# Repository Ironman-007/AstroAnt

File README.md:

# AstroAnt
Phase II of Rovables

The AstroAnt is the second generation of the Rovable project. The AstroAant also use magnetic wheels to attach to magnetic surface.

The AstroAnt is a modular design, and can carry different sensors to finish different kinds of diognostic missions, such as finding abnormal heating source, check CO2 leakage, detect metal flaw, and streaming video from remote.

Files descriptions:

- The 3D model of the robot is in the [Small_magnets_R821_with_gearbox](3dmodel/Small_magnets_R821_with_gearbox).

- The firmware of the robot is in [AstroAnt](Software/AstroAnt).

- The PC program (UI) is the [gui.py](Software/GUI_python/gui.py). Open with command line: ```python3 gui.py```

- The PCB design is in the [PCB](PCB). The [mainboard_v1](PCB/Mainboard/mainboard_v1/) is the design of the main control board, developed with KiCAD. The others are sensor modules design.

- The software of the central station for collecting data and distributing command is in [central_station](Software/Central_station/central_station/).

- The software of the central station for Camera in [cam_central](Software/Central_station/cam_central/).

- The Box design for the Zero-G flight test is in [Ant_Test_Box_DEC](3dmodel/Ant_Box_DEC/).

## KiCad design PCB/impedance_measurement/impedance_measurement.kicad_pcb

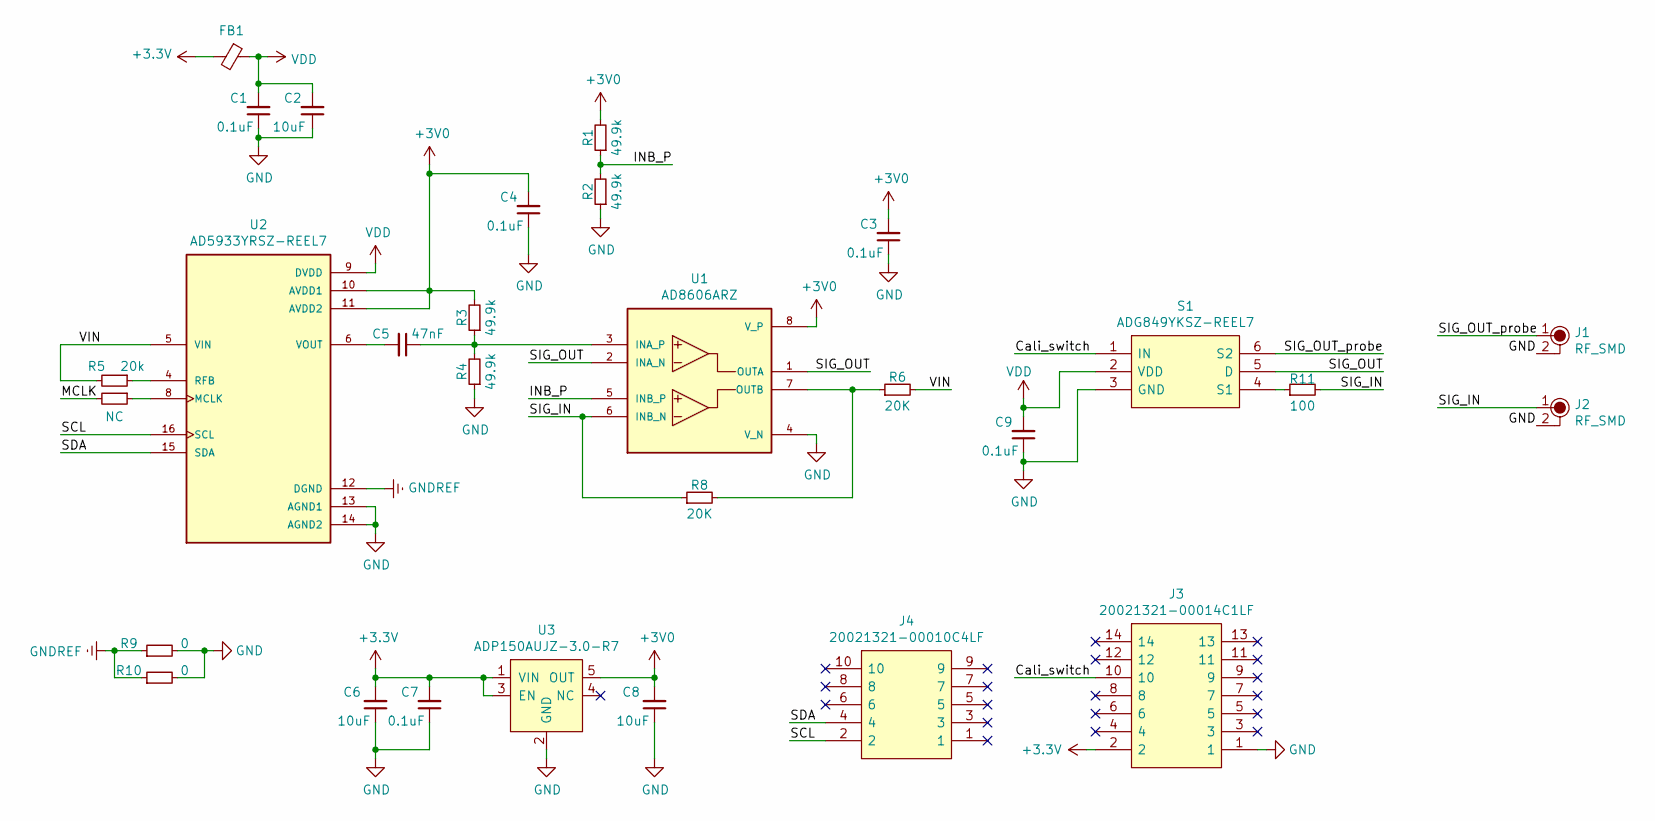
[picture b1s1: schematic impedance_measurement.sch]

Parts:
C1, C3, C4, C7, C9: 0.1uF; C_0603_1608Metric_Pad1.08x0.95mm_HandSolder
C2, C6, C8: 10uF; C_0603_1608Metric_Pad1.08x0.95mm_HandSolder
C5: 47nF; C_0402_1005Metric_Pad0.74x0.62mm_HandSolder
FB1: Ferrite_Bead_Small; C_0603_1608Metric_Pad1.08x0.95mm_HandSolder
J1, J2: RF_SMD
J3: 20021321-00014C1LF; PinHeader_2x07_P1.27mm_Vertical; Manufacturer_Part_Number 20021321-00014C1LF; Mouser Part Number 649-20213210014C1LF
J4: 20021321-00010C4LF; PinHeader_2x05_P1.27mm_Vertical; Manufacturer_Part_Number 20021321-00010C4LF; Mouser Part Number 649-202132100010C4LF
R1, R2, R3, R4: 49.9k; R_0402_1005Metric_Pad0.72x0.64mm_HandSolder
R5: 20k; R_0402_1005Metric_Pad0.72x0.64mm_HandSolder
R6: 20K; R_0402_1005Metric_Pad0.72x0.64mm_HandSolder
R7: NC; R_0402_1005Metric_Pad0.72x0.64mm_HandSolder
R8: 20K; R_0603_1608Metric_Pad0.98x0.95mm_HandSolder
R9, R10: 0; R_0402_1005Metric_Pad0.72x0.64mm_HandSolder
R11: 100; R_0805_2012Metric_Pad1.20x1.40mm_HandSolder
S1: ADG849YKSZ-REEL7; SOT65P210X110-6N; Manufacturer_Part_Number ADG849YKSZ-REEL7; Mouser Part Number 584-ADG849YKSZ-R7
U1: AD8606ARZ; SOIC127P600X175-8N; PARTREV Rev. O
U2: AD5933YRSZ-REEL7; SOP65P780X200-16N; PARTREV F
U3: ADP150AUJZ-3.0-R7; TSOT-23-5

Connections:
+3V0: C3.2, C4.2, C8.2, R1.2, R3.2, U1.8 (V_P), U2.10 (AVDD1), U2.11 (AVDD2), U3.5 (OUT)
+3V3: C6.2, C7.2, FB1.2, J3.2, U3.1 (VIN), U3.3 (EN)
/Cali_switch: J3.10, S1.1 (IN)
/INB_P: R1.1, R2.2, U1.5 (INB_P)
/SCL: J4.2, U2.16 (SCL)
/SDA: J4.4, U2.15 (SDA)
/SIG_IN: J2.1, R8.1, R11.2, U1.6 (INB_N)
/SIG_OUT: S1.5 (D), U1.1 (OUTA), U1.2 (INA_N)
/SIG_OUT_probe: J1.1, S1.6 (S2)
/VIN: R5.2, R6.2, U2.5 (VIN)
GND: C1.1, C2.1, C3.1, C4.1, C6.1, C7.1, C8.1, C9.1, J1.2, J2.2, J3.1, R2.1, R4.1, R9.2, R10.2, S1.3 (GND), U1.4 (V_N), U2.13 (AGND1), U2.14 (AGND2), U3.2 (GND)
GNDREF: R9.1, R10.1, U2.12 (DGND)
unnamed: C5.1, R3.1, R4.2, U1.3 (INA_P)
unnamed: C5.2, U2.6 (VOUT)
unnamed: R5.1, U2.4 (RFB)
unnamed: R6.1, R8.2, U1.7 (OUTB)
unnamed: R7.1, U2.8 (MCLK)
unnamed: R11.1, S1.4 (S1)
VDD: C1.2, C2.2, C9.2, FB1.1, S1.2 (VDD), U2.9 (DVDD)

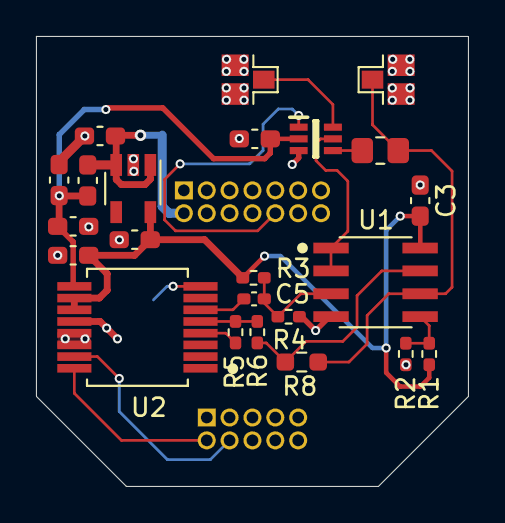
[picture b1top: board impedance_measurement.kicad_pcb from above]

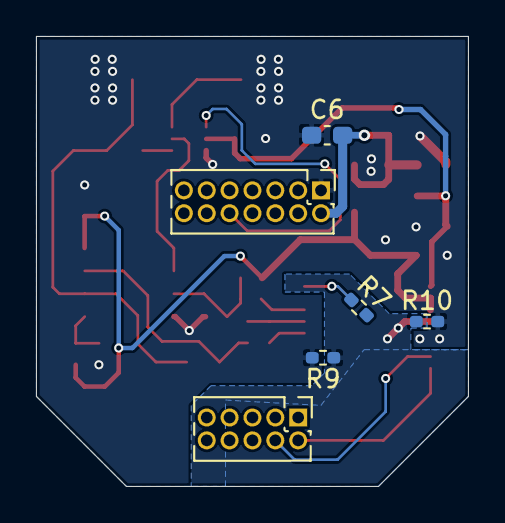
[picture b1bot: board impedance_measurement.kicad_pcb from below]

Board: 2 copper layers, 24.0 x 25.0 mm, 29 parts (6 on the bottom side), 19 nets.

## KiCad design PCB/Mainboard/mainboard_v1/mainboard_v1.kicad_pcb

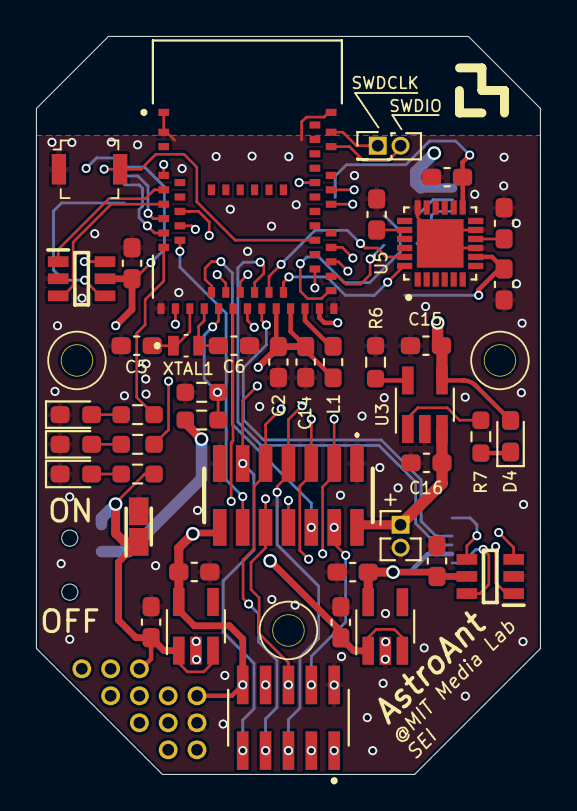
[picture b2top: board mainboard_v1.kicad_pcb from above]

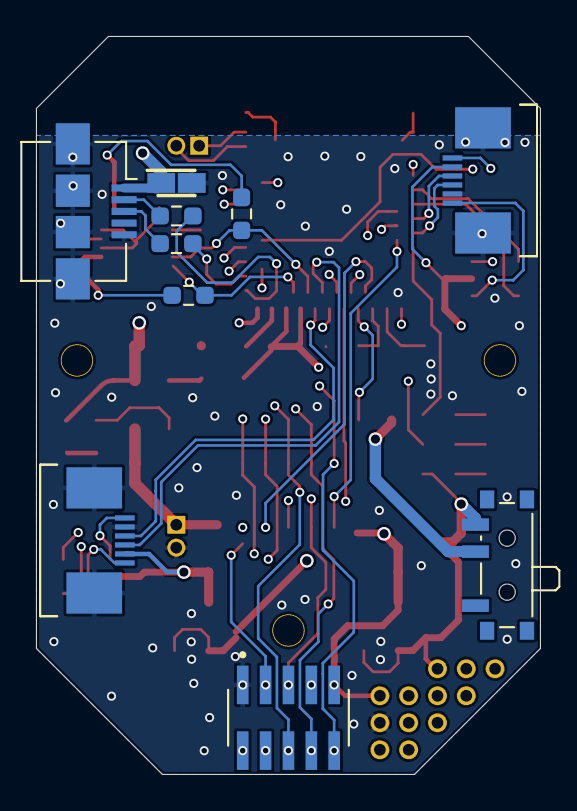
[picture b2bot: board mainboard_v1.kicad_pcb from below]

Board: 4 copper layers, 28.0 x 41.0 mm, 67 parts (10 on the bottom side), 54 nets.

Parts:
C1, C4, C8, C11, C12, C18: 0.1uF; C_0603_1608Metric_Pad1.08x0.95mm_HandSolder
C2, C10, C14, C15, C16, C17: 10uF; C_0603_1608Metric_Pad1.08x0.95mm_HandSolder
C3: 10000pF; C_0603_1608Metric_Pad1.08x0.95mm_HandSolder
C5, C6: 22PF; C_0603_1608Metric_Pad1.08x0.95mm_HandSolder
C7: 2200pF; C_0603_1608Metric_Pad1.08x0.95mm_HandSolder
C9, C13: TAJP106K010RNJ; CAPPM2014X170N
D1: LED_white; LED_0603_1608Metric_Pad1.05x0.95mm_HandSolder
D2: LED_red; LED_0603_1608Metric_Pad1.05x0.95mm_HandSolder
D3, D4: LED; LED_0603_1608Metric_Pad1.05x0.95mm_HandSolder
H1, H2, H3: M2; mounthole_1.8mm
IC1, IC2: MP6513GJ-Z; SOT95P280X100-6N
J1: 22-23-2021; PinHeader_1x02_P1.27mm_Vertical
J2: USB_B_Micro; USB_Micro-B_Amphenol_10104110_Horizontal
J3, J8: 1734592-6; 17345926
J4: 22-23-2021; PinHeader_2x01_P1.27mm_Vertical
J5, J7: 20021321-00010C4LF; HARWIN_M50-3100545
J6: 20021321-00014C1LF; 2002132100014C1LF
J9, J10, J11, J12, J13, J14, J15, J16, J17, J18, J19, J20: 1_pin_sig; 1.27mm_pin_hole
L1: 10uH; L_0603_1608Metric_Pad1.05x0.95mm_HandSolder
R1, R2: 49.9k; R_0603_1608Metric_Pad0.98x0.95mm_HandSolder
R3, R4, R5, R6: 4.99k; R_0603_1608Metric_Pad0.98x0.95mm_HandSolder
R7: 1k; R_0603_1608Metric_Pad0.98x0.95mm_HandSolder
R8, R9: 27; R_0603_1608Metric_Pad0.98x0.95mm_HandSolder
R10, R11: 10k; R_0603_1608Metric_Pad0.98x0.95mm_HandSolder
S1: B3U-1000P; Switch_Tactile_SMD_B3U-1000P
SW1: SW_SPDT; SW_SPDT_PCM12
U1: MDBT50Q-1MV2; XCVR_MDBT50Q-1MV2
U3: MCP73831T-2ACI_OT; SOT-23-5_HandSoldering
U4, U7: AP2112K-3.3; SOT-23-5_HandSoldering
U5: MPU6050; IC_MPU6050
XTAL1: 32.768KHz; ECS32712512TR

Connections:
+3V3: C1.2, C2.2, C3.2, C10.2, C14.2, J5.10, J6.14, J7.9, J11.1, L1.1, R10.2, R11.2, U1.28, U1.30, U4.5, U5.8, U5.13
/A0: R1.1, R2.2, U1.20
/A1: J5.8, J7.7, U1.21
/A3: J6.12, U1.13
/A5: J9.1, U1.9
/D5: J8.4, U1.25
/D6: J5.6, J6.10, J7.5, U1.23
/D9: J6.6, U1.19
/D11: J5.4, J6.4, J7.3, U1.22
/D12: J6.8, U1.24
/D13: J8.3, U1.26
/GP0: J18.1, U1.4
/GP2: J19.1, U1.11
/LED1: R3.2, U1.14
/LED2: R4.2, U1.16
/M1_IN1: IC1.1, U1.6
/M1_IN2: IC1.3, U1.8
/M1_O1: IC1.6, J3.6
/M1_O2: IC1.4, J3.1
/M2_IN1: IC2.1, U1.44
/M2_IN2: IC2.3, U1.46
/M2_O1: IC2.6, J8.6
/M2_O2: IC2.4, J8.1
/MISO: J5.1, J6.3, J7.2, U1.39
/MOSI: J5.3, J6.5, J7.4, U1.37
/MOTOR1_A: J3.4, U1.10
/MOTOR1_B: J3.3, U1.12
/SCK: J5.5, J6.7, J7.6, U1.36
/SCL: J5.9, J6.11, J7.10, R10.1, U1.27, U5.23
/SDA: J5.7, J6.9, J7.8, R11.1, U1.29, U5.24
/SWDCLK: J4.1, U1.53
/SWDIO: J4.2, U1.51
/SWO: J15.1, U1.47
/USB+: J2.3, R8.1
/USB-: J2.2, R9.1
/~RESET: J17.1, S1.2, U1.40
GND: C1.1, C2.1, C3.1, C4.1, C5.2, C6.2, C7.1, C8.1, C9.2, C10.1, C11.1, C12.1, C13.2, C14.1, C15.1, C16.1, C17.1, C18.1, D1.1, D2.1, D3.1, IC1.2, IC2.2, J1.2, J2.5, J2.6, J3.2, J3.MP1, J3.MP2, J5.2, J6.1, J6.13, J7.1, J8.2, J8.MP1, J8.MP2, J14.1, R2.1, R6.2, S1.1, U1.1, U1.2, U1.15, U1.33, U1.55, U3.2, U4.2, U5.9, U5.11, U5.18, U5.25, U7.2
unnamed: C4.2, U5.10
unnamed: C5.1, U1.17, XTAL1.1
unnamed: C6.1, U1.18, XTAL1.2
unnamed: C7.2, U5.20
unnamed: C9.1, C11.2, C18.2, J20.1, R5.1, SW1.3, U4.1, U4.3, U7.1, U7.3
unnamed: D1.2, R3.1
unnamed: D2.2, R4.1
unnamed: D3.2, R5.2
unnamed: D4.1, R7.1
unnamed: L1.2, U1.31
unnamed: R6.1, U3.5
unnamed: R7.2, U3.1
unnamed: R8.2, U1.35
unnamed: R9.2, U1.34
VBUS: C13.1, C15.2, D4.2, J2.1, U1.32, U3.4
VCC: C8.2, C12.2, C17.2, IC1.5, IC2.5, J3.5, J8.5, U7.5
VPP: C16.2, J1.1, J6.2, R1.2, SW1.2, U3.3

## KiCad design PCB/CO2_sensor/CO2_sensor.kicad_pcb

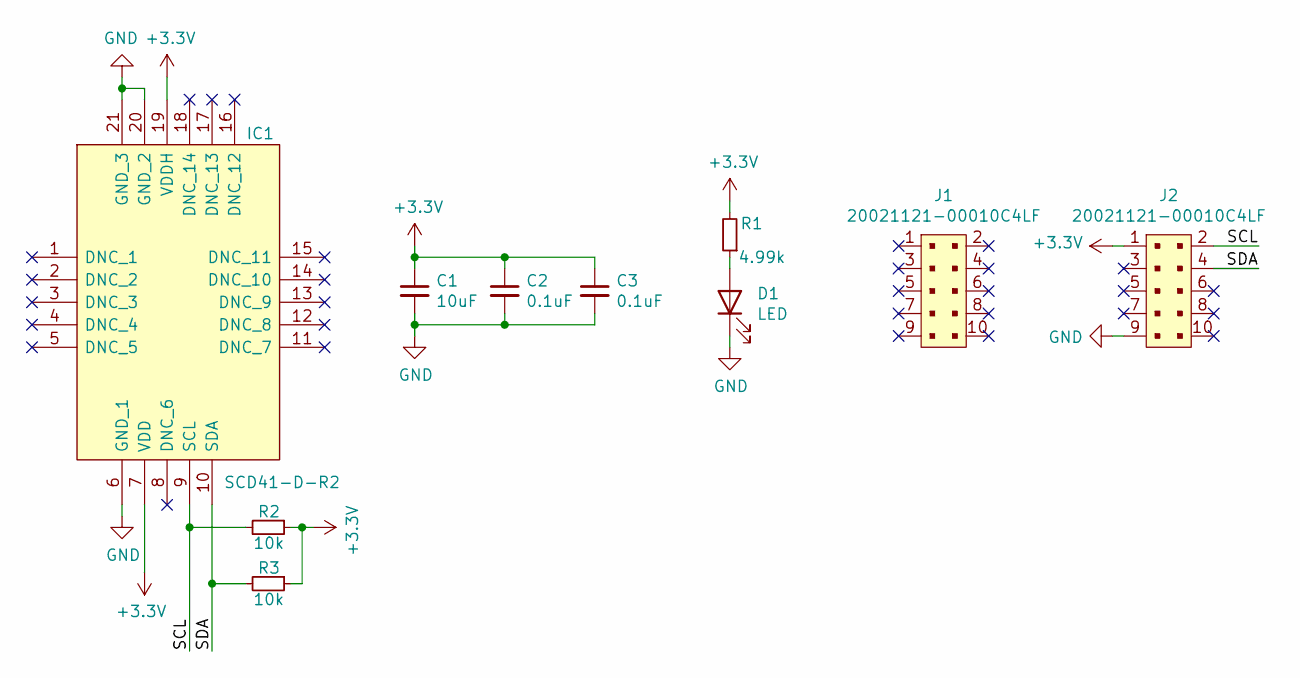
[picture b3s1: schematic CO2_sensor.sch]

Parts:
C1: 10uF; C_0603_1608Metric_Pad1.08x0.95mm_HandSolder
C2, C3: 0.1uF; C_0603_1608Metric_Pad1.08x0.95mm_HandSolder
D1: LED; LED_0603_1608Metric_Pad1.05x0.95mm_HandSolder
IC1: SCD41-D-R2; SCD41DR2; Manufacturer_Part_Number SCD41-D-R2; Mouser Part Number 403-SCD41-D-R2
J1, J2: 20021121-00010C4LF; PinHeader_2x5_P1.27mm; MPN 20021121-00010C4LF; Digi-Key_PN 609-3695-1-ND
R1: 4.99k; R_0603_1608Metric_Pad0.98x0.95mm_HandSolder
R2, R3: 10k; R_0603_1608Metric_Pad0.98x0.95mm_HandSolder

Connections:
+3V3: C1.1, C2.1, C3.1, IC1.7 (VDD), IC1.19 (VDDH), J2.1, R1.2, R2.1, R3.1
/SCL: IC1.9 (SCL), J2.2, R2.2
/SDA: IC1.10 (SDA), J2.4, R3.2
GND: C1.2, C2.2, C3.2, D1.1 (K), IC1.6 (GND_1), IC1.20 (GND_2), IC1.21 (GND_3), J2.9
unnamed: D1.2 (A), R1.1

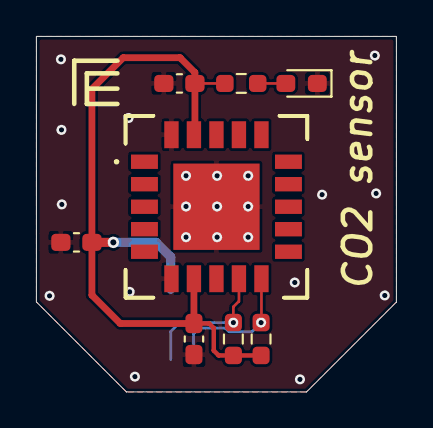
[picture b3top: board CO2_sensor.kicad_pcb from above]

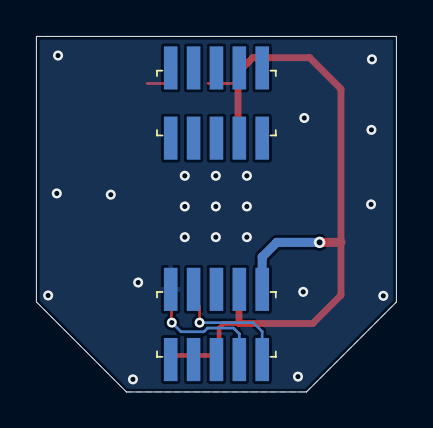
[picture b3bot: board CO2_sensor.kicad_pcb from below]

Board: 2 copper layers, 20.0 x 19.8 mm, 10 parts (2 on the bottom side), 5 nets.

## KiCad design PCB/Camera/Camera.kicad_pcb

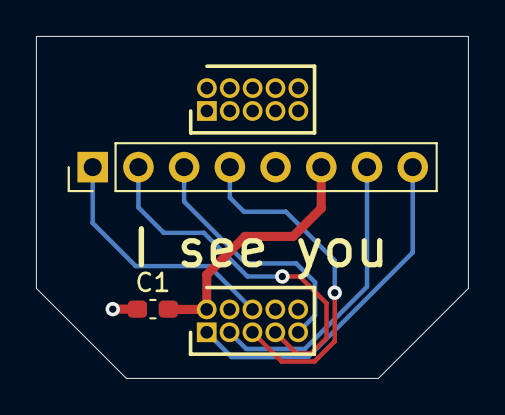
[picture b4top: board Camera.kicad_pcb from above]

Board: 2 copper layers, 24.0 x 19.0 mm, 4 parts (0 on the bottom side), 8 nets.

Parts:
C1: 0.1uF; C_0603_1608Metric_Pad1.08x0.95mm_HandSolder
J1, J2: GRPB052VWVN-RC; HDRV10W50P127_2X5_635X340X430P
U1: Arducam_OV2640_module; PinHeader_1x08_P2.54mm_Vertical

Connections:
+3V3: C1.1, J1.2, U1.6
/CS: J1.6, U1.1
/MISO: J1.9, U1.3
/MOSI: J1.7, U1.2
/SCK: J1.5, U1.4
/SCL: J1.1, U1.8
/SDA: J1.3, U1.7
GND: C1.2, J1.10, U1.5

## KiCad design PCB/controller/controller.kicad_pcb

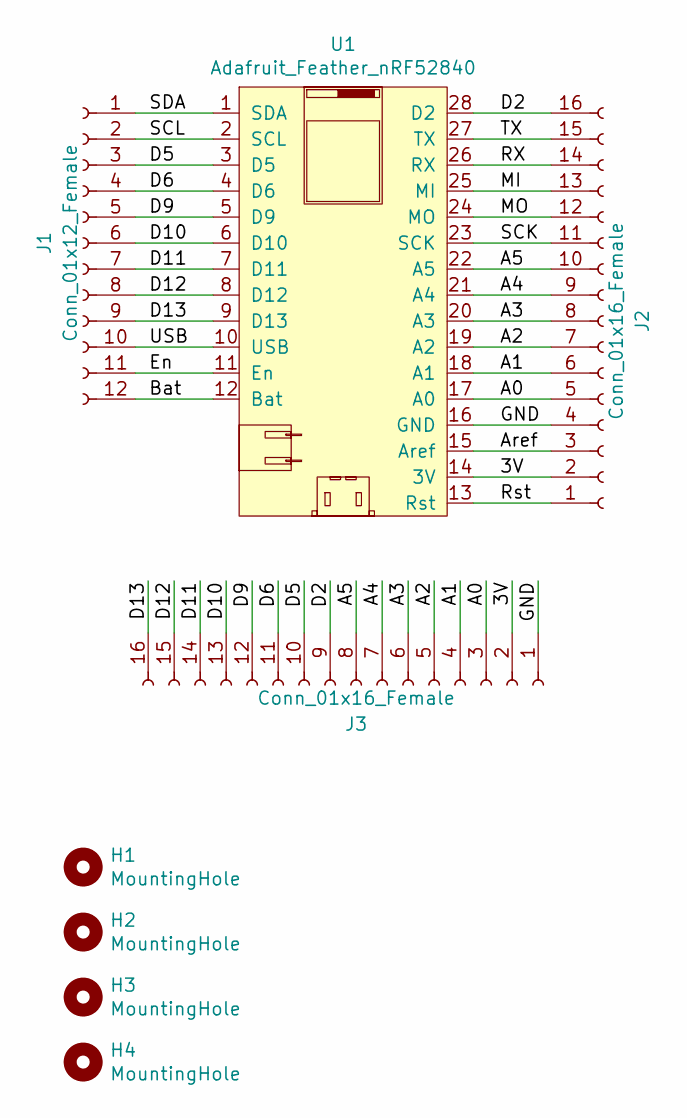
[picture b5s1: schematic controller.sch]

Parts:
H1, H2, H3, H4: MountingHole; MountingHole_2.2mm_M2
J1: Conn_01x12_Female; PinHeader_1x12_P2.54mm_Vertical
J2: Conn_01x16_Female; PinHeader_1x16_P2.54mm_Vertical
J3: Conn_01x16_Female; PinHeader_1x16_P2.54mm_Horizontal
U1: Adafruit_Feather_nRF52840; Adafruit_feather_nRF52840

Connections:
/3V: J2.2, J3.2, U1.14 (3V)
/A0: J2.5, J3.3, U1.17 (A0)
/A1: J2.6, J3.4, U1.18 (A1)
/A2: J2.7, J3.5, U1.19 (A2)
/A3: J2.8, J3.6, U1.20 (A3)
/A4: J2.9, J3.7, U1.21 (A4)
/A5: J2.10, J3.8, U1.22 (A5)
/Aref: J2.3, U1.15 (Aref)
/Bat: J1.12, U1.12 (Bat)
/D2: J2.16, J3.9, U1.28 (D2)
/D5: J1.3, J3.10, U1.3 (D5)
/D6: J1.4, J3.11, U1.4 (D6)
/D9: J1.5, J3.12, U1.5 (D9)
/D10: J1.6, J3.13, U1.6 (D10)
/D11: J1.7, J3.14, U1.7 (D11)
/D12: J1.8, J3.15, U1.8 (D12)
/D13: J1.9, J3.16, U1.9 (D13)
/En: J1.11, U1.11 (En)
/GND: J2.4, J3.1, U1.16 (GND)
/MI: J2.13, U1.25 (MI)
/MO: J2.12, U1.24 (MO)
/RX: J2.14, U1.26 (RX)
/Rst: J2.1, U1.13 (Rst)
/SCK: J2.11, U1.23 (SCK)
/SCL: J1.2, U1.2 (SCL)
/SDA: J1.1, U1.1 (SDA)
/TX: J2.15, U1.27 (TX)
/USB: J1.10, U1.10 (USB)

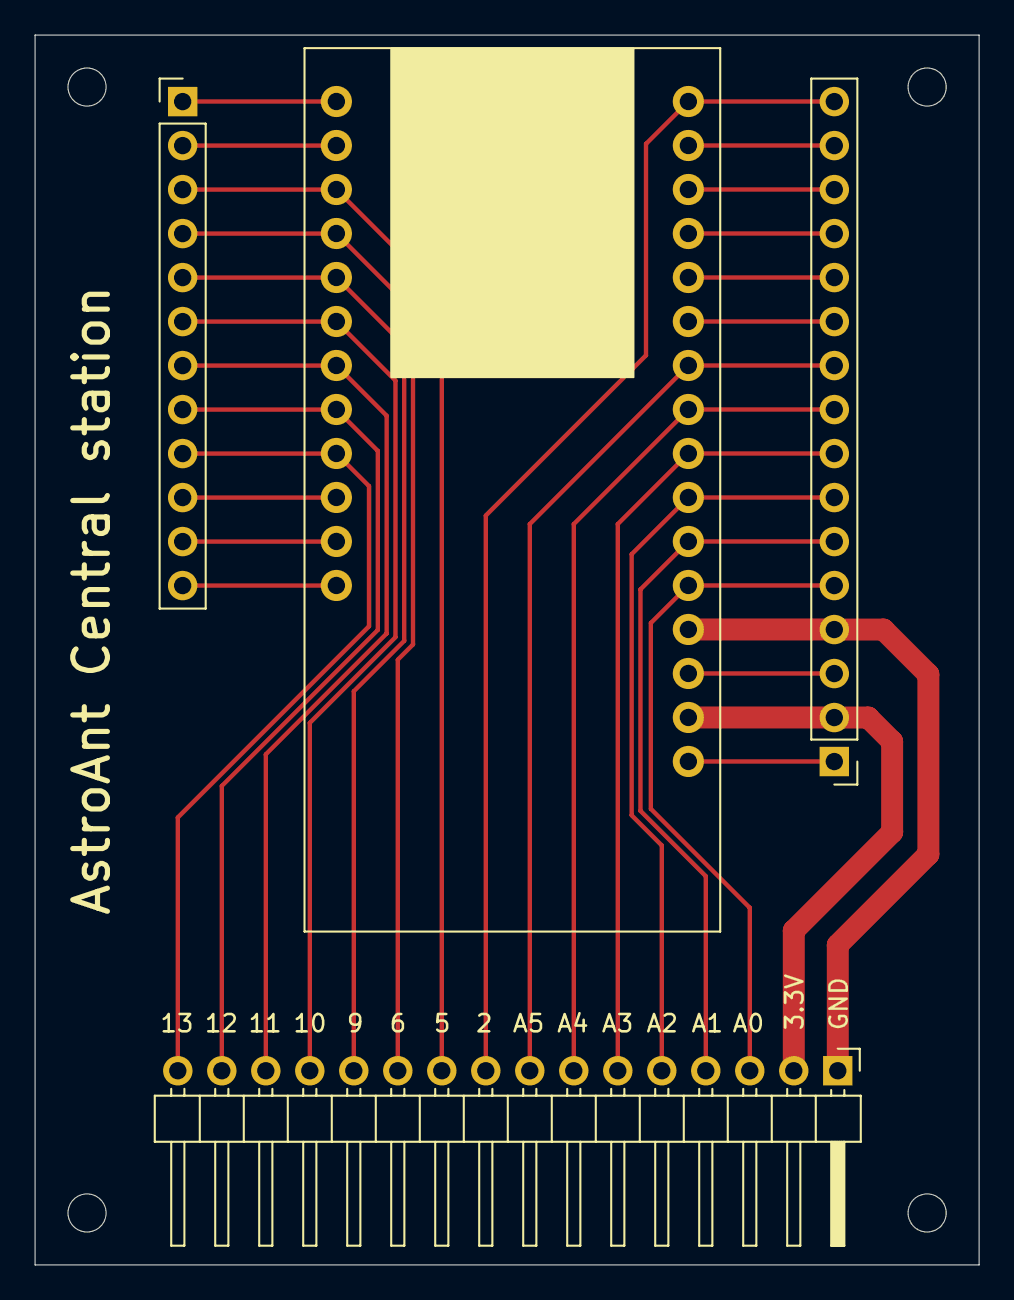
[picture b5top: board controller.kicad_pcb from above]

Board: 2 copper layers, 54.5 x 71.0 mm, 8 parts (0 on the bottom side), 28 nets.

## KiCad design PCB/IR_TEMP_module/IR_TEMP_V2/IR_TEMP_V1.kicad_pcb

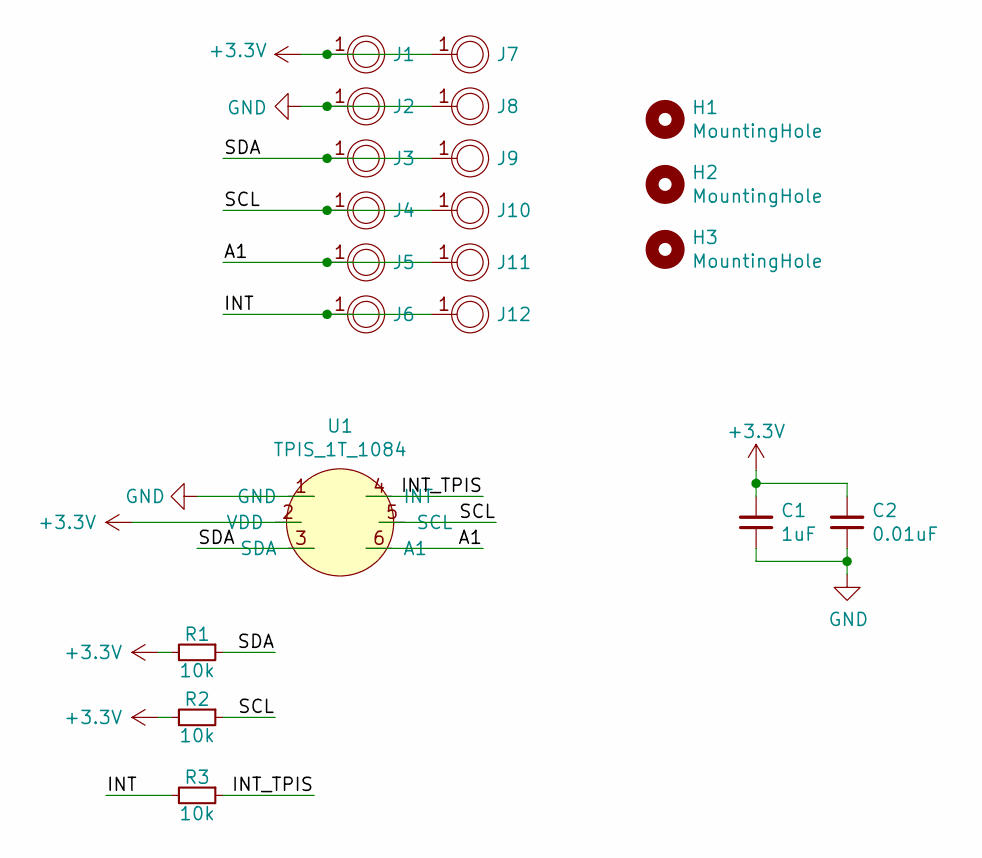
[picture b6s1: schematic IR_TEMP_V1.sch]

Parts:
C1: 1uF; C_0402_1005Metric_Pad0.74x0.62mm_HandSolder
C2: 0.01uF; C_0402_1005Metric_Pad0.74x0.62mm_HandSolder
H1, H2, H3: MountingHole; M1.6_mounthole
J1, J2, J3, J4, J5, J6, J7, J8, J9, J10, J11, J12: 1_PIN; 1_pin_SMD_1.5mmx1.0mm
R1, R2, R3: 10k; R_0402_1005Metric_Pad0.72x0.64mm_HandSolder
U1: TPIS_1T_1084

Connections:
+3V3: C1.2, C2.2, J1.1, J7.1, R1.2, R2.2, U1.2 (VDD)
/A1: J5.1, J11.1, U1.6 (A1)
/INT: J6.1, J12.1, R3.2
/INT_TPIS: R3.1, U1.4 (INT)
/SCL: J4.1, J10.1, R2.1, U1.5 (SCL)
/SDA: J3.1, J9.1, R1.1, U1.3 (SDA)
GND: C1.1, C2.1, J2.1, J8.1, U1.1 (GND)

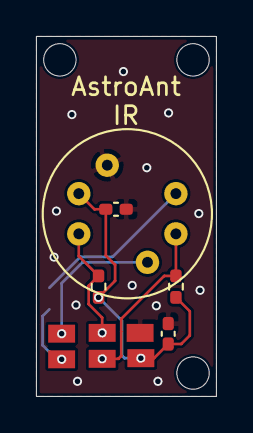
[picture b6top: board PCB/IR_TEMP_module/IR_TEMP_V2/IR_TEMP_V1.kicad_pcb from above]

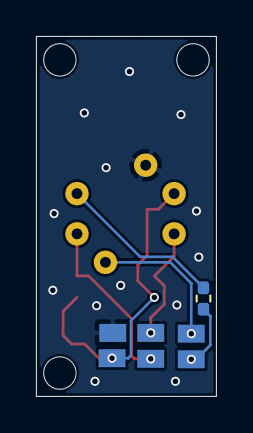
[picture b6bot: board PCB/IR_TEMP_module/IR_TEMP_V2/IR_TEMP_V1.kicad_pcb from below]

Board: 2 copper layers, 10.0 x 20.0 mm, 21 parts (7 on the bottom side), 7 nets.

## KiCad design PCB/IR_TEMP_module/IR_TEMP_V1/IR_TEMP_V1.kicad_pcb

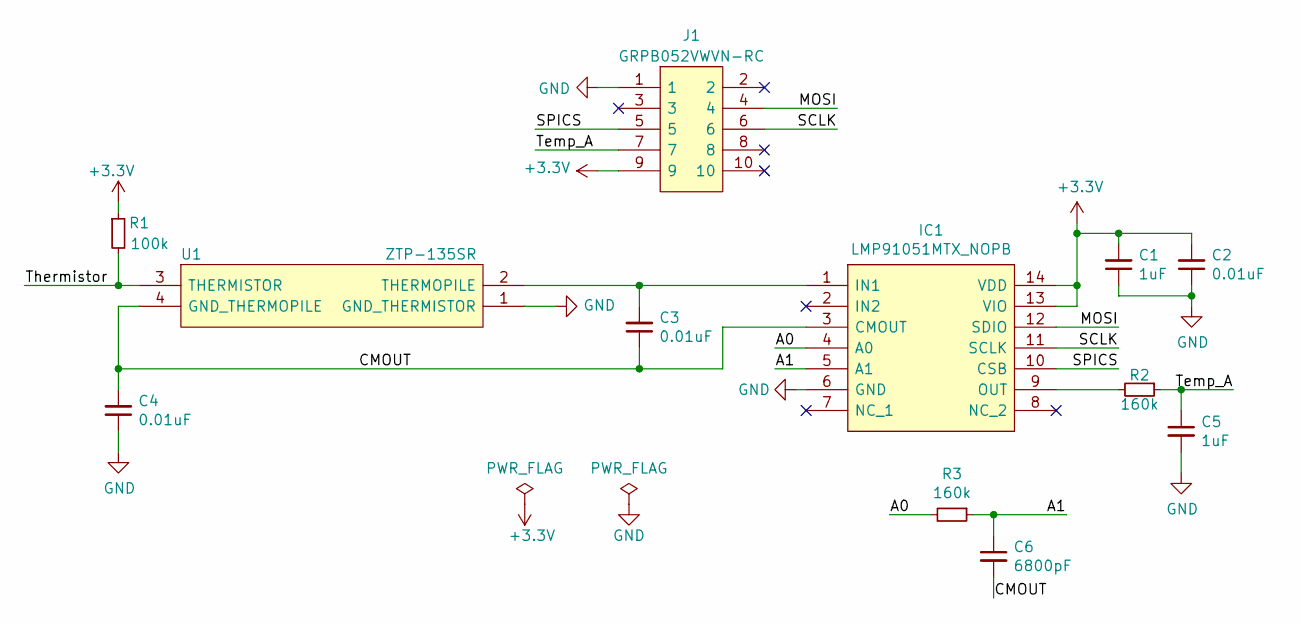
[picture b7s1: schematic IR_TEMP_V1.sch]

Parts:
C1, C5: 1uF; C_0402_1005Metric_Pad0.74x0.62mm_HandSolder
C2, C3, C4: 0.01uF; C_0402_1005Metric_Pad0.74x0.62mm_HandSolder
C6: 6800pF; C_0603_1608Metric_Pad1.08x0.95mm_HandSolder
IC1: LMP91051MTX_NOPB; SOP65P640X120-14N; Manufacturer_Part_Number LMP91051MTX/NOPB; Mouser Part Number 595-LMP91051MTX/NOPB
J1: GRPB052VWVN-RC; HDRV10W50P127_2X5_635X340X430P; Manufacturer_Part_Number GRPB052VWVN-RC
R1: 100k; R_0402_1005Metric_Pad0.72x0.64mm_HandSolder
R2: 160k; R_0402_1005Metric_Pad0.72x0.64mm_HandSolder
R3: 160k; R_0603_1608Metric_Pad0.98x0.95mm_HandSolder
U1: ZTP-135SR; TO-46-4; Manufacturer_Part_Number ZTP-135SR; Mouser Part Number 527-ZTP-135SR

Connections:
+3V3: C1.2, C2.2, IC1.13 (VIO), IC1.14 (VDD), J1.9, R1.1
/A0: IC1.4 (A0), R3.2
/A1: C6.1, IC1.5 (A1), R3.1
/CMOUT: C3.1, C4.2, C6.2, IC1.3 (CMOUT), U1.4 (GND_THERMOPILE)
/MOSI: IC1.12 (SDIO), J1.4
/SCLK: IC1.11 (SCLK), J1.6
/SPICS: IC1.10 (CSB), J1.5
/Temp_A: C5.1, J1.7, R2.1
/Thermistor: R1.2, U1.3 (THERMISTOR)
GND: C1.1, C2.1, C4.1, C5.2, IC1.6 (GND), J1.1, U1.1 (GND_THERMISTOR)
unnamed: C3.2, IC1.1 (IN1), U1.2 (THERMOPILE)
unnamed: IC1.9 (OUT), R2.2

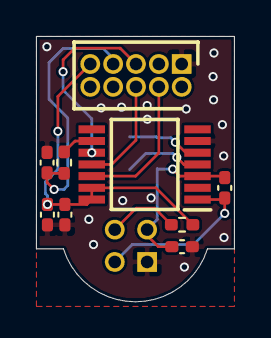
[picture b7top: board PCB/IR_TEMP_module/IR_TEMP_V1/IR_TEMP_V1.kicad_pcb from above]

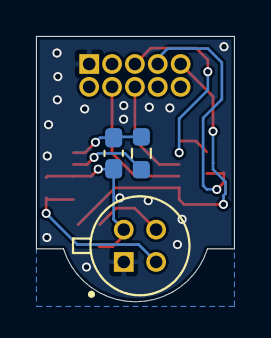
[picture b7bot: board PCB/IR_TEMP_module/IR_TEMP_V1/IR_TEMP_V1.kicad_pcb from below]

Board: 2 copper layers, 11.0 x 14.7 mm, 12 parts (3 on the bottom side), 12 nets.

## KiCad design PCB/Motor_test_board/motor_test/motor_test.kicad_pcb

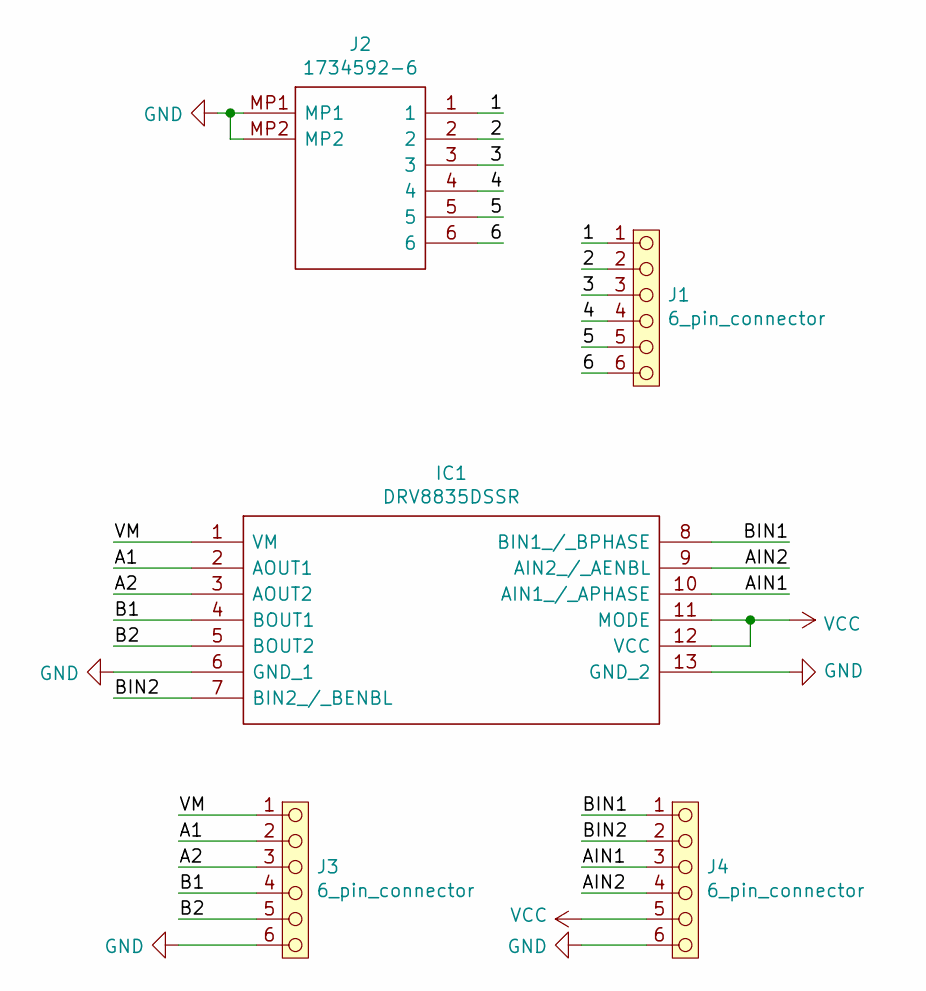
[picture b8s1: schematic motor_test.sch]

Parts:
IC1: DRV8835DSSR; Manufacturer_Part_Number DRV8835DSSR; Mouser Part Number 595-DRV8835DSSR
J1, J3, J4: 6_pin_connector; PinHeader_1x06_P2.54mm_Vertical
J2: 1734592-6; 17345926; Manufacturer_Part_Number 1734592-6; Mouser Part Number 571-1734592-6

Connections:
/1: J1.1, J2.1
/2: J1.2, J2.2
/3: J1.3, J2.3
/4: J1.4, J2.4
/5: J1.5, J2.5
/6: J1.6, J2.6
/A1: IC1.2 (AOUT1), J3.2
/A2: IC1.3 (AOUT2), J3.3
/AIN1: IC1.10 (AIN1_/_APHASE), J4.3
/AIN2: IC1.9 (AIN2_/_AENBL), J4.4
/B1: IC1.4 (BOUT1), J3.4
/B2: IC1.5 (BOUT2), J3.5
/BIN1: IC1.8 (BIN1_/_BPHASE), J4.1
/BIN2: IC1.7 (BIN2_/_BENBL), J4.2
/VM: IC1.1 (VM), J3.1
GND: IC1.6 (GND_1), IC1.13 (GND_2), J2.MP1, J2.MP2, J3.6, J4.6
VCC: IC1.11 (MODE), IC1.12 (VCC), J4.5

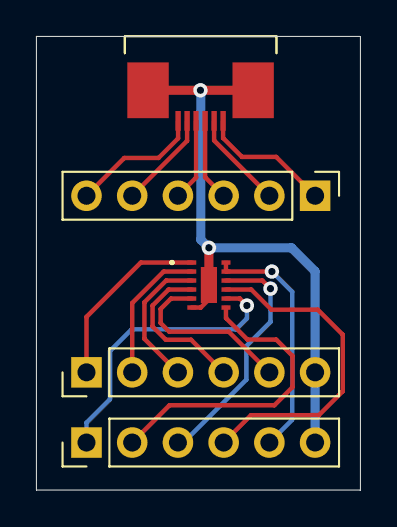
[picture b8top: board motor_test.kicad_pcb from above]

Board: 2 copper layers, 18.0 x 25.2 mm, 5 parts (0 on the bottom side), 17 nets.

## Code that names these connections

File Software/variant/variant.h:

 /*
  Copyright (c) 2014-2015 Arduino LLC.  All right reserved.
  Copyright (c) 2016 Sandeep Mistry All right reserved.
  Copyright (c) 2018, Adafruit Industries (adafruit.com)

  This library is free software; you can redistribute it and/or
  modify it under the terms of the GNU Lesser General Public
  License as published by the Free Software Foundation; either
  version 2.1 of the License, or (at your option) any later version.
  This library is distributed in the hope that it will be useful,
  but WITHOUT ANY WARRANTY; without even the implied warranty of
  MERCHANTABILITY or FITNESS FOR A PARTICULAR PURPOSE.
  See the GNU Lesser General Public License for more details.
  You should have received a copy of the GNU Lesser General Public
  License along with this library; if not, write to the Free Software
  Foundation, Inc., 51 Franklin St, Fifth Floor, Boston, MA  02110-1301  USA
*/

#ifndef _VARIANT_FEATHER52840_
#define _VARIANT_FEATHER52840_

/** Master clock frequency */
#define VARIANT_MCK       (64000000ul)

#define USE_LFXO      // Board uses 32khz crystal for LF
// define USE_LFRC    // Board uses RC for LF

/*----------------------------------------------------------------------------
 *        Headers
 *----------------------------------------------------------------------------*/

#include "WVariant.h"

#ifdef __cplusplus
extern "C"
{
#endif // __cplusplus

// Number of pins defined in PinDescription array
#define PINS_COUNT           (34)
#define NUM_DIGITAL_PINS     (34)
#define NUM_ANALOG_INPUTS    (6) // A6 is used for battery, A7 is analog reference
#define NUM_ANALOG_OUTPUTS   (0)

// LEDs
#define PIN_LED1             (3)
#define PIN_LED2             (4)
#define PIN_NEOPIXEL         (8)
#define NEOPIXEL_NUM         1

#define LED_BUILTIN          PIN_LED1
#define LED_CONN             PIN_LED2

#define LED_RED              PIN_LED1
#define LED_BLUE             PIN_LED2

#define LED_STATE_ON         1         // State when LED is litted

/*
 * Buttons
 */
#define PIN_BUTTON1          (7)

/*
 * Analog pins
 */
#define PIN_A0               (14)
#define PIN_A1               (15)
#define PIN_A2               (16)
#define PIN_A3               (17)
#define PIN_A4               (18)
#define PIN_A5               (19)
#define PIN_A6               (20)
#define PIN_A7               (21)

static const uint8_t A0  = PIN_A0 ;
static const uint8_t A1  = PIN_A1 ;
static const uint8_t A2  = PIN_A2 ;
static const uint8_t A3  = PIN_A3 ;
static const uint8_t A4  = PIN_A4 ;
static const uint8_t A5  = PIN_A5 ;
static const uint8_t A6  = PIN_A6 ;
static const uint8_t A7  = PIN_A7 ;
#define ADC_RESOLUTION    14

// Other pins
#define PIN_AREF           PIN_A7
#define PIN_VBAT           PIN_A6
#define PIN_NFC1           (33)
#define PIN_NFC2           (2)

static const uint8_t AREF = PIN_AREF;

/*
 * Serial interfaces
 */
#define PIN_SERIAL1_RX       (1)
#define PIN_SERIAL1_TX       (0)

/*
 * SPI Interfaces
 */
#define SPI_INTERFACES_COUNT 1

#define PIN_SPI_MISO         (24)
#define PIN_SPI_MOSI         (25)
#define PIN_SPI_SCK          (26)

static const uint8_t SS   = (5);
static const uint8_t MOSI = PIN_SPI_MOSI ;
static const uint8_t MISO = PIN_SPI_MISO ;
static const uint8_t SCK  = PIN_SPI_SCK ;

/*
 * Wire Interfaces
 */
#define WIRE_INTERFACES_COUNT 1

#define PIN_WIRE_SDA         (22)
#define PIN_WIRE_SCL         (23)

// QSPI Pins FZ
// #define PIN_QSPI_SCK         27
// #define PIN_QSPI_CS          28
// #define PIN_QSPI_IO0         29
// #define PIN_QSPI_IO1         30
// #define PIN_QSPI_IO2         31
// #define PIN_QSPI_IO3         32

// motor control
#define M1_IN1       (27)
#define M1_IN2       (28)

#define M2_IN1       (29)
#define M2_IN2       (30)

// Encoder
#define Encoder_A1   (20)
#define Encoder_B1   (21)

#define Encoder_A2   (5)
#define Encoder_B2   (13)

// On-board QSPI Flash
#define EXTERNAL_FLASH_DEVICES   GD25Q16C
#define EXTERNAL_FLASH_USE_QSPI

#ifdef __cplusplus
}
#endif

/*----------------------------------------------------------------------------
 *        Arduino objects - C++ only
 *----------------------------------------------------------------------------*/

#endif

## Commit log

2021-08-02 udated by FZ
2021-11-13 updated by FZ
